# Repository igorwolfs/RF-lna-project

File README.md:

# RF-LNA-Project
This repo contains the kicad-schematics and simulations for 3 separate projects.

[Design, simulation and verification of an 868 MHz, 2-Stage Cascode amplifier](resources/lna/README.md)

[Design, simulation and verification of an 868 MHz Meandered Monopole antenna](https://github.com/igorwolfs/RF-simulations/tree/main/rf_simulations/lorawan_meandered_monopole)

[Design, simulation and verification of an 868 MHz, Single-Gain Stage amplifier](resources/lna/README.md)

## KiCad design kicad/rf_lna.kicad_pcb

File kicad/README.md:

# KiCad Schematics

## Cascode and Single-Gain Stage
### Input voltage
Assume a max input voltage of 1 mV (close to the transceiver) at 868 MHz.
Given a gain of 25 dB.

### Current variation
Current amplitude is somewhere between 18.4 -> 25.6 mA at the oscillation frequency (which is pretty huge).

So required charge over half a period is (25.6-18.4) * (T/2) =  (25.6-18.4)e-3/ (868e6 * 2) = 4.15 pC

Make sure the capacitor arrays carry at least that amount of charge at 5 V.
So 4.15 pC / 5 V < 1 pF, so the capacitor needs to be at least 1 pF (easy).

### Supply voltage
Pick 5 V supply voltage with component L78L05 (cheap, basic component).

Add LED to verify power ON.

### Capacitors
Capacitor Q-factor: capacitor's reactance / capacitor's parasitic resistance.
- The bigger Q, the smaller the ESR relative to the reactance, the better.

### Inductors
Finding a good AC blocking inductor that is
- About 100 nH
- Self resonant-frequency beyond 2 GHz
Seems to be quite the task

### Resistor size
- Always choose smallest package with relevant power rating, to minimize parasitics.
- Probably good up to a few GHz, once going above 2 GHz make sure to get specialized once.

### Thermal relieves
To make soldering the matching components easier, use thermal relieves.

## Antenna

### Design
#### Matching circuit
Estimated using [SimNec](https://www.ae6ty.com/smith_charts/) and [OpenEMS](https://www.openems.de/).

#### CPW to antenna transition
Non-ideal, was a guess based on a quick search for ideal impedance transition methods.

### Simulations
Simulation data for the antenna can be found inside the [rf-simulations repo](https://github.com/igorwolfs/RF-simulations/tree/main/rf_simulations/lorawan_meandered_monopole).

### Verification
Initial verification results using a NanoVNA show similar results to the OpenEMS simulation.

## JLCPCB Stackup
The jlcpcb-[trace impedance calculator](https://jlcpcb.com/pcb-impedance-calculator
) tool was used for trace thickness calculations for our coplanar waveguide. Stackup: JLC04161H-3313 (economic PCBA).

For the following stackup:
- L1: CU: 0.035 mm
- prepreg: 0.2104 mm prepreg
- L2: 0.0152 mm copper
- Core: 1.065 mm
- L3: 0.0152 mm copper
- Prepreg: 7628, RC 49 %, 0.2104 mm
- L4: CU: 0.035 mm

Use a coplanar waveguide.
- distance to surrounding ground: 0.3 mm
- Trace width: 0.3244 mm
    -> So the total CPW is about 0.3244+0.6 = 0.9244 mm.
    -> We do have enough space however so that should not be an issue.

Note: to much distance between GND and trace requires the trace to become wider.

## Checks before ordering
- Component check: 
    - Do all components have the expected value
    - Do all components have the expected footprint size
- Gerber check:
    - Are the groundplanes adequately removed, is there ground plane where there needs to be.
    - Are the components connected as they are supposed to?

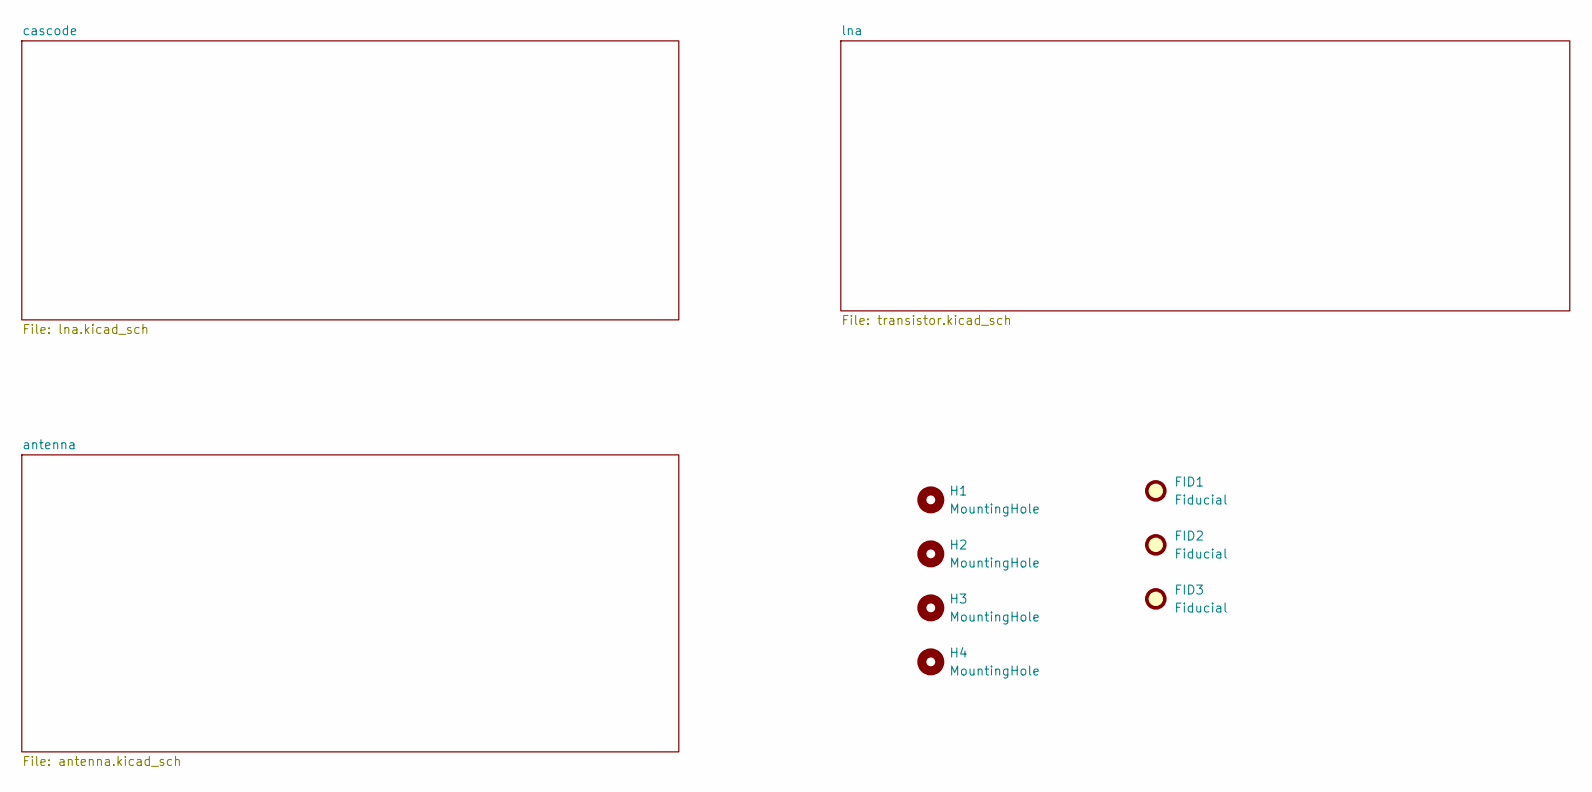
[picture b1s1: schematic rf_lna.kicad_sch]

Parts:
FID1, FID2, FID3: Fiducial; Fiducial_1mm_Mask2mm
H1, H2, H3, H4: MountingHole; MountingHole_1.152mm_jlcpcb

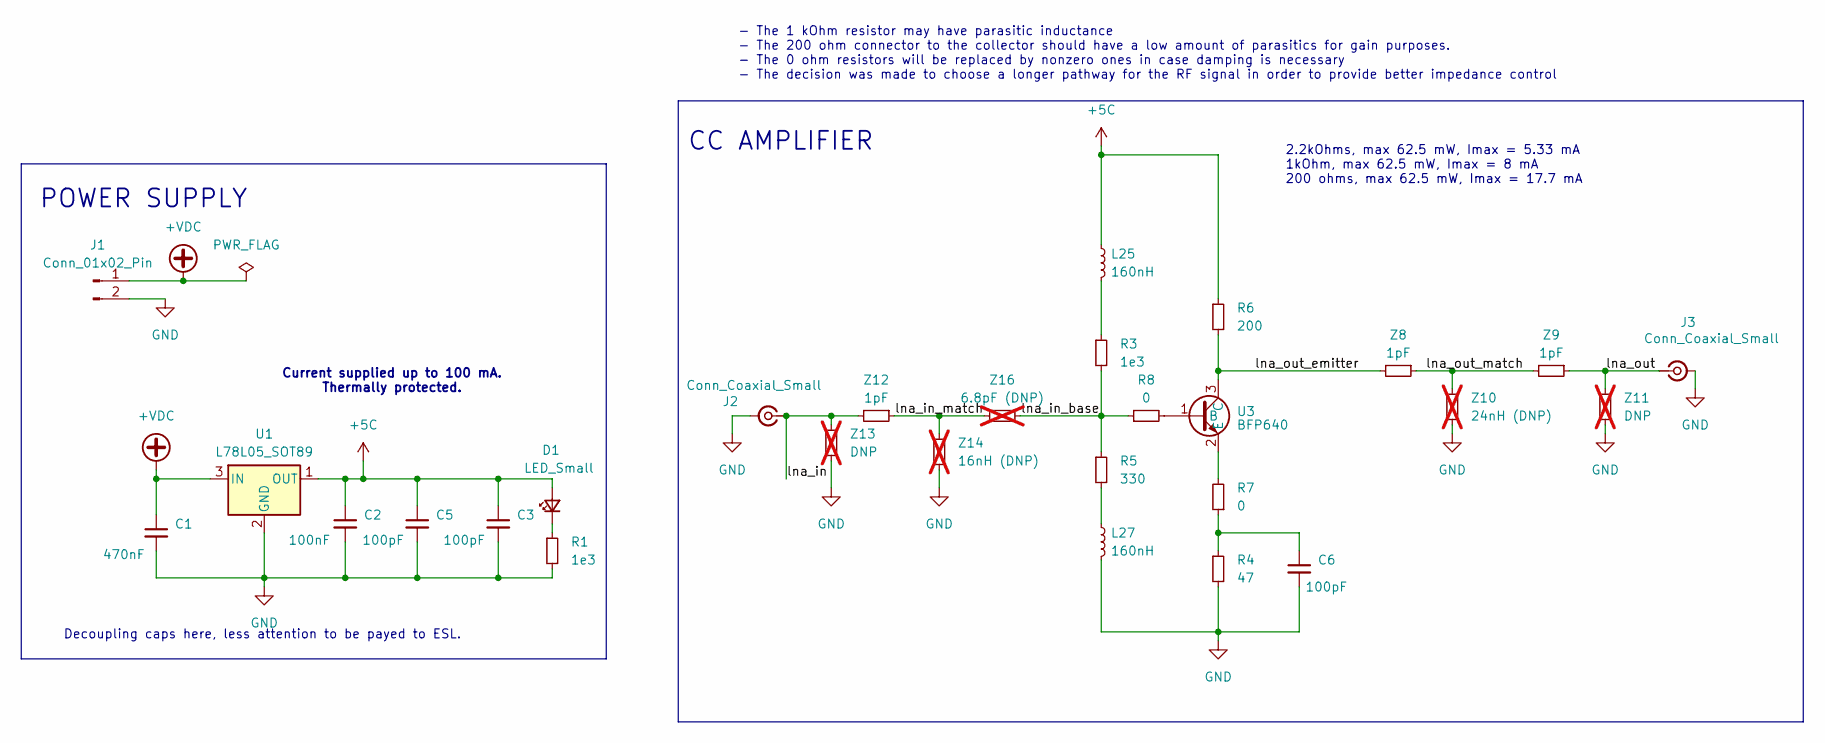
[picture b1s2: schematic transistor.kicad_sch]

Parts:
C1: 470nF; C_0603_1608Metric; Manufacturing Part Numb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 CL10B474KA8NNNC; LCSC Part Number C1623
C2: 100nF; C_0402_1005Metric; Manufacturing Part Numb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 CL05B104KO5NNNC; LCSC Part Number C1525
C3, C5, C6: 100pF; C_0402_1005Metric; Manufacturing Part Numb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 0402CG101J500NT; LCSC Part Number C1546
D1: LED_Small; LED_0603_1608Metric; Manufacturing Part Numb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 KT-0603R; LCSC Part Number C2286
J1: Conn_01x02_Pin; SolderWire-0.25sqmm_1x02_P4.2mm_D0.65mm_OD1.7mm
J2, J3: Conn_Coaxial_Small; SMA_Amphenol_901-143_Vertical; Manufacturing Part Numb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 BWSMA-KE-Z001; LCSC Part Number C496549
L25, L27: 160nH; L_0603_1608Metric; Manufacturing Part Numb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 LQW18ANR16J00D; LCSC Part Number C140445
R1, R3: 1e3; R_0402_1005Metric; Manufacturing Part Numb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 0402WGF1001TCE; LCSC Part Number C11702
R4: 47; R_0603_1608Metric; Manufacturing Part Numb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 0603WAF470JT5E; LCSC Part Number C23182
R5: 330; R_0402_1005Metric; Manufacturing Part Numb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 0402WGF3300TCE; LCSC Part Number C25104
R6: 200; R_0402_1005Metric; Manufacturing Part Numb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 0402WGF2000TCE; LCSC Part Number C25087
R7, R8: 0; R_0402_1005Metric_Pad0.72x0.64mm_HandSolder; Manufacturing Part Numb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 0402WGF0000TCE; LCSC Part Number C17168
U1: L78L05_SOT89; SOT-89-3; Manufacturing Part Numb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 78L05G-AB3-R; LCSC Part Number C71136
U3: BFP640; Manufacturing Part Numb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 BFP640H6327; LCSC Part Number C439781
Z8, Z9, Z12: 1pF; R_0402_1005Metric_Pad0.72x0.64mm_HandSolder; Manufacturing Part Numb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 0402CG1R0C500NT; LCSC Part Number C1550
Z10: 24nH (DNP); R_0402_1005Metric_Pad0.72x0.64mm_HandSolder; not fitted
Z11, Z13: DNP; R_0402_1005Metric_Pad0.72x0.64mm_HandSolder; not fitted
Z14: 16nH (DNP); R_0402_1005Metric_Pad0.72x0.64mm_HandSolder; not fitted
Z16: 6.8pF (DNP); R_0402_1005Metric_Pad0.72x0.64mm_HandSolder; not fitted

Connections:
+5C: C2.1, C3.1, C5.1, D1.2 (A), L25.1, R6.1, U1.1 (OUT)
+VDC: C1.1, J1.1, U1.3 (IN)
/lna/lna_in: J2.1 (In), Z12.2, Z13.2
/lna/lna_in_base: R3.2, R5.1, R8.1, Z16.1
/lna/lna_in_match: Z12.1, Z14.2, Z16.2
/lna/lna_out: J3.1 (In), Z9.1, Z11.2
/lna/lna_out_emitter: R6.2, U3.3 (C), Z8.2
/lna/lna_out_match: Z8.1, Z9.2, Z10.2
GND: C1.2, C2.2, C3.2, C5.2, C6.2, J1.2, J2.2 (Ext), J3.2 (Ext), L27.2, R1.2, R4.2, U1.2 (GND), Z10.1, Z11.1, Z13.1, Z14.1; also elsewhere on the board
unnamed: C6.1, R4.1, R7.1
unnamed: D1.1 (K), R1.1
unnamed: L25.2, R3.1
unnamed: L27.1, R5.2
unnamed: R8.2, U3.1 (B)
unnamed: R7.2, U3.2 (E)

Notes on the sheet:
Current supplied up to 100 mA. Thermally protected.
2.2kOhms, max 62.5 mW, Imax = 5.33 mA 1kOhm, max 62.5 mW, Imax = 8 mA 200 ohms, max 62.5 mW, Imax = 17.7 mA
CC AMPLIFIER
POWER SUPPLY
Decoupling caps here, less attention to be payed to ESL.
- The 1 kOhm resistor may have parasitic inductance - The 200 ohm connector to the collector should have a low amount of parasitics for gain purposes. - The 0 ohm resistors will be replaced by nonzero ones in case damping is necessary - The decision was made to choose a longer pathway for the RF si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

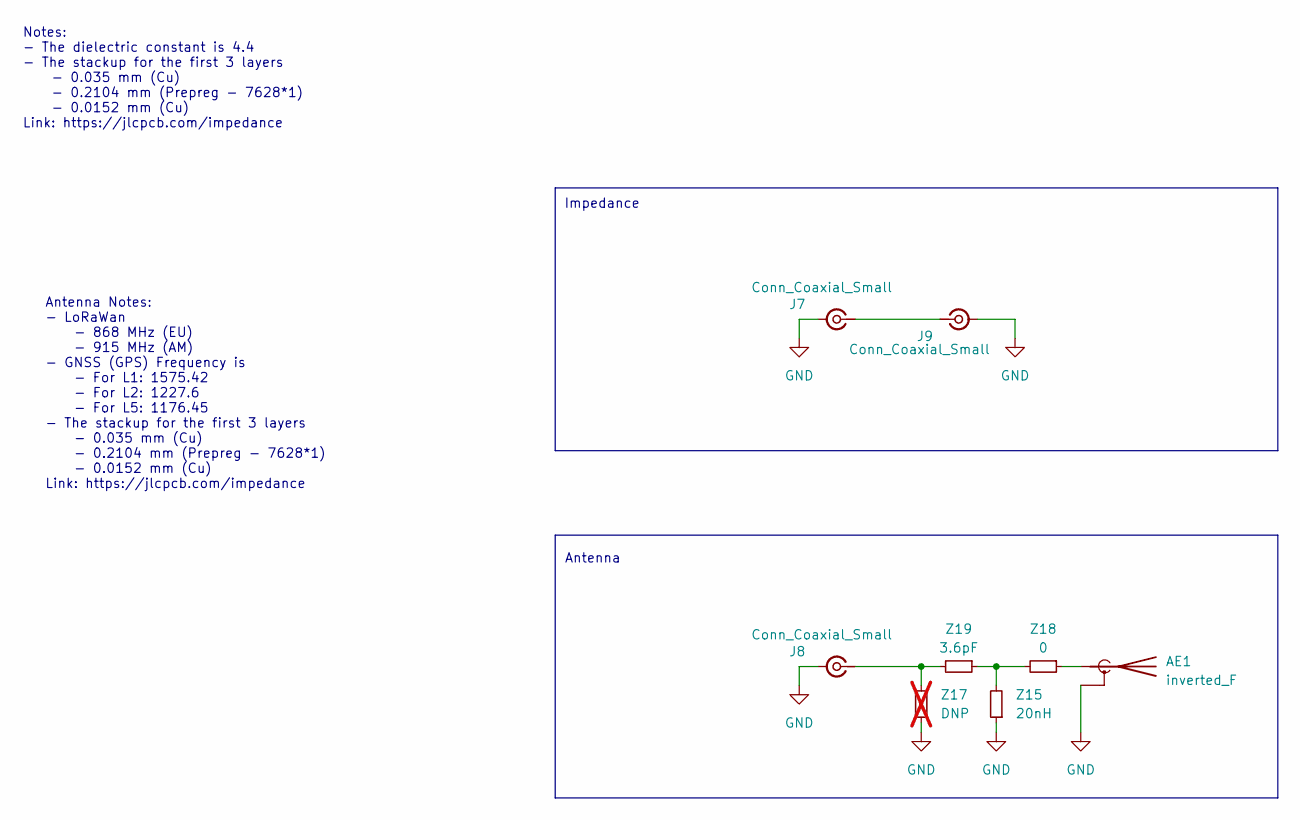
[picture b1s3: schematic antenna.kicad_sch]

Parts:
AE1: inverted_F; iw_meandered_monopole
J7, J8, J9: Conn_Coaxial_Small; SMA_Amphenol_901-143_Vertical; Manufacturing Part Numb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 BWSMA-KE-Z001; LCSC Part Number C496549
Z15: 20nH; R_0402_1005Metric_Pad0.72x0.64mm_HandSolder; Manufacturing Part Numb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 SDCL1005C20NJTDF; LCSC Part Number C96730
Z17: DNP; R_0402_1005Metric_Pad0.72x0.64mm_HandSolder; not fitted
Z18: 0; R_0402_1005Metric_Pad0.72x0.64mm_HandSolder; Manufacturing Part Numb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 0402WGF0000TCE; LCSC Part Number C17168
Z19: 3.6pF; R_0402_1005Metric_Pad0.72x0.64mm_HandSolder; Manufacturing Part Numb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 GJM1555C1H3R6WB01D; LCSC Part Number C161321

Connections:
GND: AE1.2 (GND), J7.2 (Ext), J8.2 (Ext), J9.2 (Ext), Z15.1, Z17.1; also elsewhere on the board
unnamed: AE1.1 (A), Z18.1
unnamed: J7.1 (In), J9.1 (In)
unnamed: J8.1 (In), Z17.2, Z19.2
unnamed: Z15.2, Z18.2, Z19.1

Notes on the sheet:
Antenna
Impedance
Antenna Notes: - LoRaWan - 868 MHz (EU) - 915 MHz (AM) - GNSS (GPS) Frequency is - For L1: 1575.42 - For L2: 1227.6 - For L5: 1176.45 - The stackup for the first 3 layers - 0.035 mm (Cu) - 0.2104 mm (Prepreg - 7628*1) - 0.0152 mm (Cu) Link: https://jlcpcb.com/impedance
Notes: - The dielectric constant is 4.4 - The stackup for the first 3 layers - 0.035 mm (Cu) - 0.2104 mm (Prepreg - 7628*1) - 0.0152 mm (Cu) Link: https://jlcpcb.com/impedance

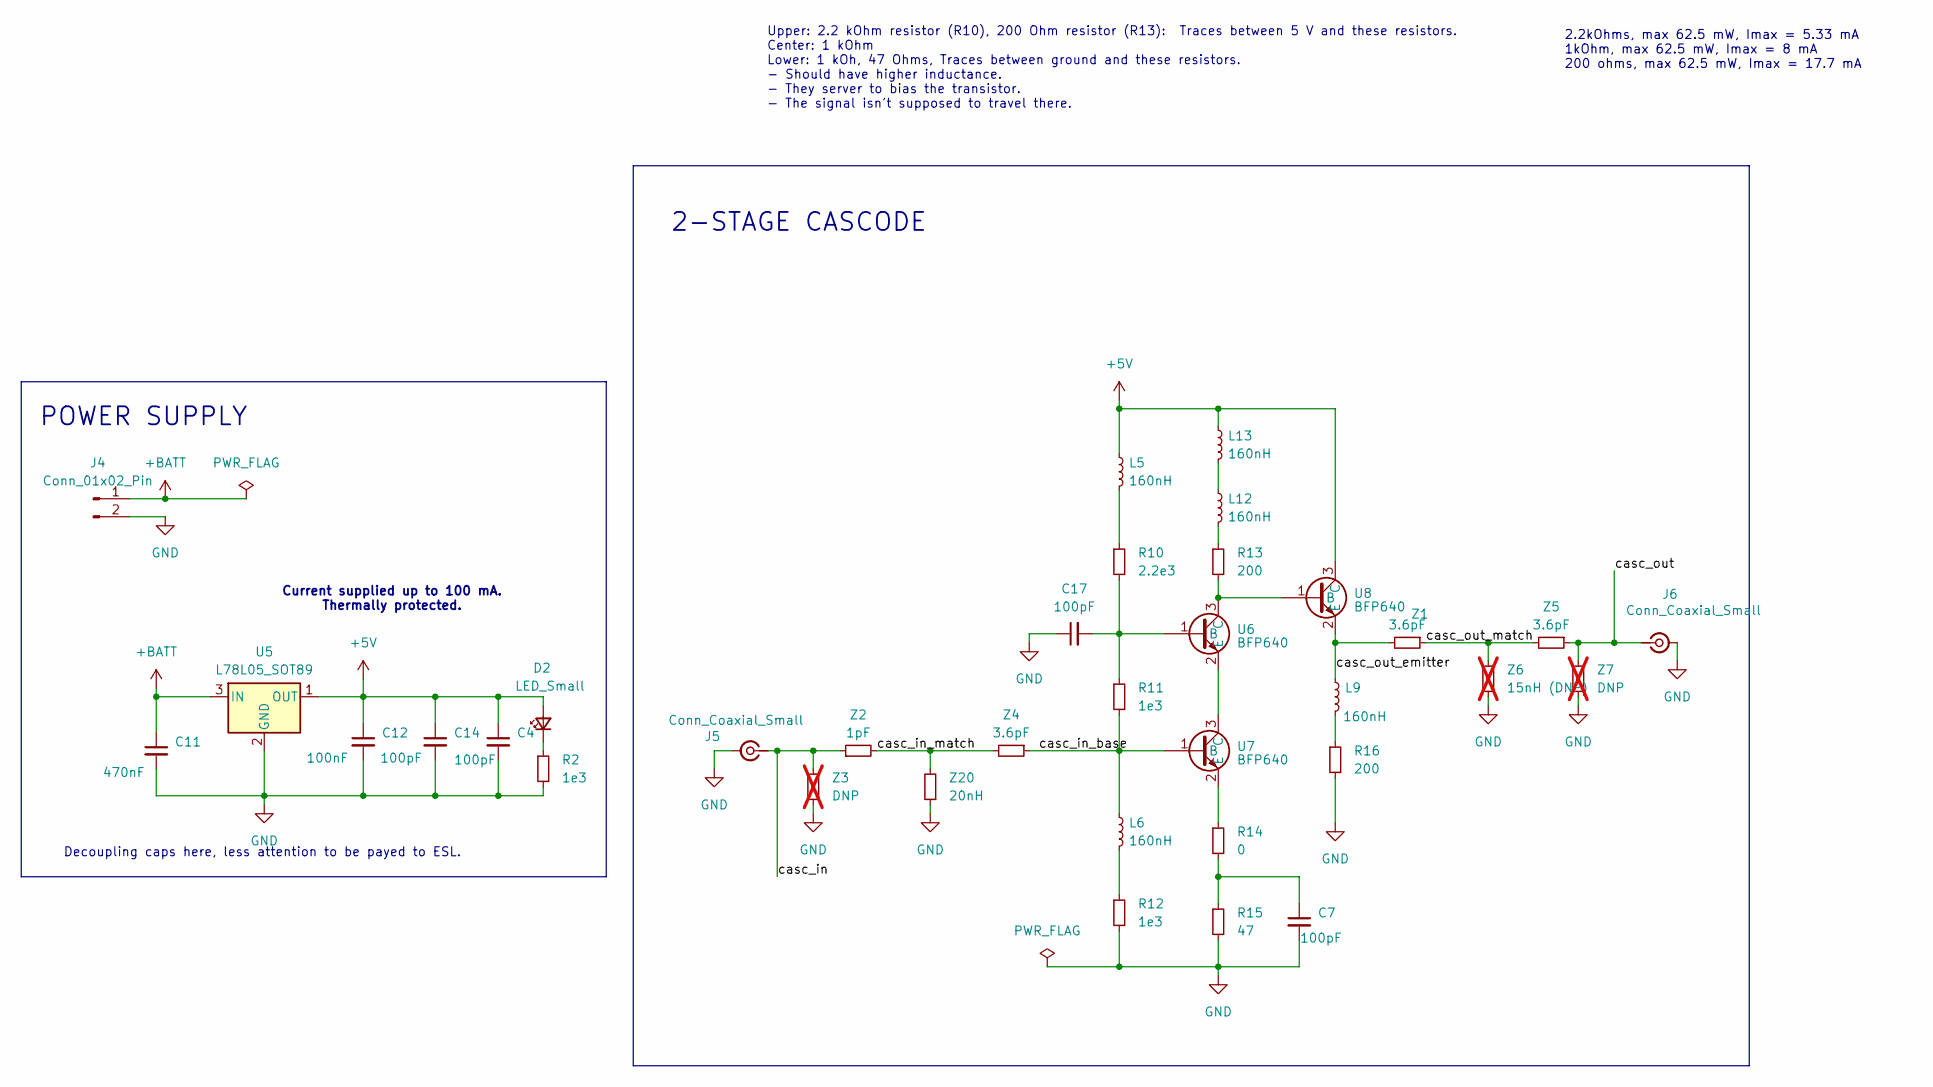
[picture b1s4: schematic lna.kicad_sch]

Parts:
C4, C7, C14, C17: 100pF; C_0402_1005Metric; Manufacturing Part Numb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 0402CG101J500NT; LCSC Part Number C1546
C11: 470nF; C_0603_1608Metric; Manufacturing Part Numb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 CL10B474KA8NNNC; LCSC Part Number C1623
C12: 100nF; C_0402_1005Metric; Manufacturing Part Numb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 CL05B104KO5NNNC; LCSC Part Number C1525
D2: LED_Small; LED_0603_1608Metric; Manufacturing Part Numb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 KT-0603R; LCSC Part Number C2286
J4: Conn_01x02_Pin; SolderWire-0.25sqmm_1x02_P4.2mm_D0.65mm_OD1.7mm
J5, J6: Conn_Coaxial_Small; SMA_Amphenol_901-143_Vertical; Manufacturing Part Numb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 BWSMA-KE-Z001; LCSC Part Number C496549
L5, L6, L9, L12, L13: 160nH; L_0603_1608Metric; Manufacturing Part Numb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 LQW18ANR16J00D; LCSC Part Number C140445
R2, R11, R12: 1e3; R_0402_1005Metric; Manufacturing Part Numb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 0402WGF1001TCE; LCSC Part Number C11702
R10: 2.2e3; R_0402_1005Metric; Manufacturing Part Numb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 0402WGF2201TCE; LCSC Part Number C25879
R13, R16: 200; R_0402_1005Metric; Manufacturing Part Numb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 0402WGF2000TCE; LCSC Part Number C25087
R14: 0; R_0402_1005Metric_Pad0.72x0.64mm_HandSolder; Manufacturing Part Numb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 0402WGF0000TCE; LCSC Part Number C17168
R15: 47; R_0603_1608Metric; Manufacturing Part Numb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 0603WAF470JT5E; LCSC Part Number C23182
U5: L78L05_SOT89; SOT-89-3; Manufacturing Part Numb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 78L05G-AB3-R; LCSC Part Number C71136
U6, U7, U8: BFP640; Manufacturing Part Numb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 BFP640H6327; LCSC Part Number C439781
Z1, Z4, Z5: 3.6pF; R_0402_1005Metric_Pad0.72x0.64mm_HandSolder; Manufacturing Part Numb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 GJM1555C1H3R6WB01D; LCSC Part Number C161321
Z2: 1pF; R_0402_1005Metric_Pad0.72x0.64mm_HandSolder; Manufacturing Part Numb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 0402CG1R0C500NT; LCSC Part Number C1550
Z3, Z7: DNP; R_0402_1005Metric_Pad0.72x0.64mm_HandSolder; not fitted
Z6: 15nH (DNP); R_0402_1005Metric_Pad0.72x0.64mm_HandSolder; not fitted
Z20: 20nH; R_0402_1005Metric_Pad0.72x0.64mm_HandSolder; Manufacturing Part Numb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 SDCL1005C20NJTDF; LCSC Part Number C96730

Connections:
+5V: C4.1, C12.1, C14.1, D2.2 (A), L5.1, L13.1, U5.1 (OUT), U8.3 (C)
+BATT: C11.1, J4.1, U5.3 (IN)
/cascode/casc_in: J5.1 (In), Z2.1, Z3.1
/cascode/casc_in_base: L6.1, R11.2, U7.1 (B), Z4.1
/cascode/casc_in_match: Z2.2, Z4.2, Z20.2
/cascode/casc_out: J6.1 (In), Z5.1, Z7.2
/cascode/casc_out_emitter: L9.1, U8.2 (E), Z1.2
/cascode/casc_out_match: Z1.1, Z5.2, Z6.2
GND: C4.2, C7.2, C11.2, C12.2, C14.2, C17.1, J4.2, J5.2 (Ext), J6.2 (Ext), R2.2, R12.2, R15.2, R16.2, U5.2 (GND), Z3.2, Z6.1, Z7.1, Z20.1; also elsewhere on the board
unnamed: C7.1, R14.2, R15.1
unnamed: D2.1 (K), R2.1
unnamed: L5.2, R10.1
unnamed: L6.2, R12.1
unnamed: L9.2, R16.1
unnamed: L12.1, L13.2
unnamed: L12.2, R13.1
unnamed: C17.2, R10.2, R11.1, U6.1 (B)
unnamed: R13.2, U6.3 (C), U8.1 (B)
unnamed: U6.2 (E), U7.3 (C)
unnamed: R14.1, U7.2 (E)

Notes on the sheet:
2-STAGE CASCODE
2.2kOhms, max 62.5 mW, Imax = 5.33 mA 1kOhm, max 62.5 mW, Imax = 8 mA 200 ohms, max 62.5 mW, Imax = 17.7 mA
Upper: 2.2 kOhm resistor (R10), 200 Ohm resistor (R13): Traces between 5 V and these resistors. Center: 1 kOhm Lower: 1 kOh, 47 Ohms, Traces between ground and these resistors. - Should have higher inductance. - They server to bias the transistor. - The signal isn't supposed to travel there.
Current supplied up to 100 mA. Thermally protected.
Decoupling caps here, less attention to be payed to ESL.
POWER SUPPLY

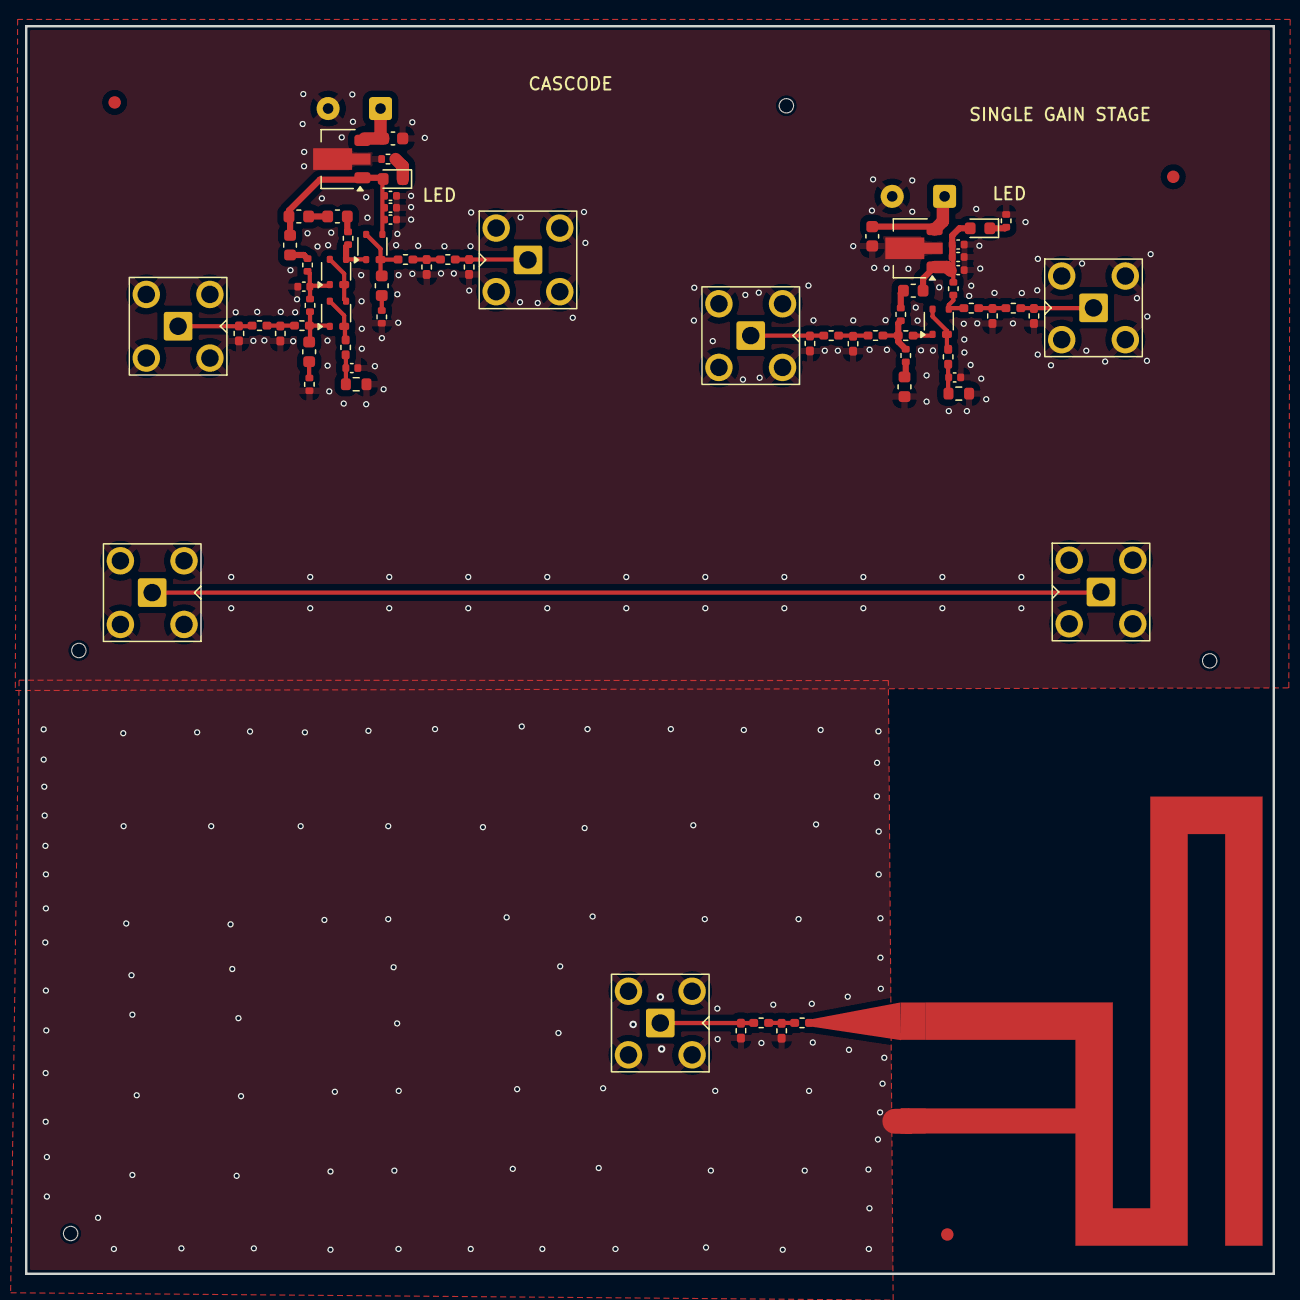
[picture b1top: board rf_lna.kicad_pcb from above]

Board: 4 copper layers, 100.0 x 100.0 mm, 78 parts (0 on the bottom side), 38 nets.

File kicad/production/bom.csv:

Designator,Footprint,Quantity,Value,LCSC Part #
AE1,iw_meandered_monopole,1,inverted_F,
"C1, C11",603,2,470nF,
"C12, C2",402,2,100nF,
"C14, C17, C3, C4, C5, C6, C7",402,7,100pF,
"D1, D2",603,2,LED_Small,
"J1, J4",SolderWire-0.25sqmm_1x02_P4.2mm_D0.65mm_OD1.7mm,2,Conn_01x02_Pin,
"J2, J3, J5, J6, J7, J8, J9",SMA_Amphenol_901-143_Vertical,7,Conn_Coaxial_Small,
"L12, L13, L25, L27, L5, L6, L9",603,7,160nH,
"R1, R11, R12, R2, R3",402,5,1.00E+03,
R10,402,1,2.20E+03,
"R13, R16, R6",402,3,200,
"R14, R7, R8, Z18",402,4,0,
"R15, R4",603,2,47,
R5,402,1,330,
"U1, U5",SOT-89-3,2,L78L05_SOT89,
"U3, U6, U7, U8",BFP640,4,BFP640,
"Z1, Z19, Z4, Z5",402,4,3.6pF,
"Z12, Z2, Z8, Z9",402,4,1pF,
"Z15, Z20",402,2,20nH,

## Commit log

2024-09-24 added notes, added datasheets, | TODO: check how stability analyisis is done, choose BJT, make prototype circuit
2024-09-24 added gitignore
2024-09-24 removed application notes for space reasons
2024-09-25 added notes
2024-09-28 [simulatinos] Did some basic experiments [resources] Tried calculating resistor values, currents and voltages, erroneous results however
2024-10-01 updated gitignore
2024-10-01 [resources] Added (correct) LNA calculations assuming infinite load, added stability calculations [simulations] Added single stage LNA simulations for 3.3 and 5 V Vcc
2024-10-01 [resources] Added emitter-follower dimensioning | TODO: answer questions in notebook + simulate emitter-follower circuit
2024-10-02 [simulations] Added emitter follower simulations, added frequency sweep simulation | TODO: figure out how to get absolute dB values referenced to the gain in ltspice, check the gain-input-amplitude c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
2024-10-03 [simulations] Fixed gain problem for low amplitudes | TODO: complete small-signal circuit for 2-stage LNA
2024-10-06 [simulations] Added cacscode amplifier, did input impedance matching, checked stability, checked s-parameters, did noise simulations | TODO: check actual noise factor simulations
2024-10-06 Fix the bias-T's in the noise-test simulation or look for example simulations for such test circuits
2024-10-08 [simulations] Noise factor simulation complete | TODO: introduce matching circuits, match impedances and recalculate reflection, transmission, noise, etc..
2024-10-08 finished impedance matching and S-parameter analysis
2024-12-07 [simulations] Simply added rf-netlist [lna_schematics] Started with kicad schematic
2024-12-07 minor changes
2024-12-18 [simulations] Added L-matching networks | TODO: find wide-band matching T / Pi matching circuits (800MHz -> 1.5 GHz), find actual working components for the circuit
2024-12-18 test
2024-12-19 [lna_schematics] Simulated with matched impedance to get voltage values and verify matching parameters [lna_schematics] Added matched elements, added notes
2024-12-20 [kicad] Added various footprints, added matched network
2024-12-20 [simualations] Added simulations for components matching
2024-12-20 [general] Added notes
2024-12-20 [lna_schematics] added final components for impedance matching [simulations] Added final impedance matched simulations | TODO: stackup + layout + footprint check
2024-12-20 [kicad] Finished pads, stackup, symbols for LNA. Starting layout.
2024-12-20 [kicad] Implemement custom design rule for CPW
2024-12-20 [simulations] Switched bypass capacitor to new value
2024-12-21 [simulations] Added extra simulations with inductors | TODO: match impedance with inductors
2024-12-21 [lna_schematics] Added single-transistor LNA to schematics | TODO: update footprint and matched impedance with inductors
2024-12-21 [simulations] Did simulations with matching circuits | TODO: figure out a way to lower the S22 while including a capacitor filter. Check why exactly adding inductors causes the S22 here to be so high
2024-12-23 [lna_schematics] Added components for matching + inductances | TODO: place inductors to prevent capacitive coupling [simulations] Added stability factor and matching circuits | TODO: do bilateral mat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
2024-12-24 [simulations] Did full impedance matching, changed inductors to 160 nH instead of 91
2024-12-24 [rf_lna] did layout of rf amplifiers for LNA | TODO: create an antenna design for the bottom half
2024-12-25 [kicad] Did placement of lna components, added antenna | TODO: connect traces, add extra trace for impedance check, add antenna
2024-12-28 [kicad] Added antenna footprint to PCB | TODO: simulate and then add the antenna to the gerber as a whole
2025-01-09 impedance checks + minor changes
2025-01-12 changed gitignore
2025-01-12 [simulations] Moved simulations for antenna into folder
2025-01-12 [simulations] Reorganized ltspice simulations, checked use of transmission line simulation, checked stability and asked stability question
2025-01-12 removed simulation data
2025-01-12 [review] Added questions for review
2025-01-12 reorganized kicad schematics
2025-01-12 [kicad] Added routing, antenna footprint creation, via stitching, fencing, added extra matching footprints, removed footprints from BOM -> perform matching on receipt of PCB itself, added 78 mm - 50 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
2025-01-12 [kicad] Removed excess dimensioning on antenna, added extra vias around sma connector
2025-01-13 added pictures of boards and reddit message. Added 3D models in kicad
2025-01-18 files ready for production, but with wrong stackup (3313)
2025-01-18 placed jlcpcb order, waiting for gerber confirmation
2025-03-22 [minor] Added LNA readme
2025-03-24 [feat] Cleaned up README's
2025-04-01 [bringup] Added calibration data for 2-port and single-port system with coax, added markdown
2025-04-02 [bringup] Added antenna measurement results and todos
2025-04-03 [minor] Added todo's for next version
2025-04-03 [bringup] Added 2-port VNA measurements version 1 and 2, added comments for first antenna matching step, changed antenna calibration data [next] Check reason for single-gain stage failure
2025-04-03 [bringup] Added notes on transistor operating mode [next] Calculate matching circuits, add soldering bridge to lna
2025-04-04 [bringup] Got RF matching circuit, added todo's and next steps for future circuits, [next] Merging 2-way s-parameter circuits
2025-04-05 [bringup - antenna] Optimal matching verification and rematch using scikit-rf lib
2025-04-05 [bringup] Added stability check + gain check for LNA [next] Create a model of the LNA using the S-parameters from the website, check the model results vs real results, see where best to apply damping
2025-04-05 [bringup] Checked stability conditions (mu, rollet, circles), added s-parameter data for simulation purposes [next] Interpolate and simulate the single-gain stage, do the same with the LNA, check LNA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
2025-04-05 [minor] Changed readme
2025-04-06 [bringup] Added interpolation of transistor parameters, added 3rd port, building circuits for the single-gain stage
2025-04-06 [bringup] Cleaned up code, put everything into single python-libs repo, added s-port transform resource, added transforms from common-emitter to common-base and common-collector
2025-04-07 [bringup] Finished circuit drawing, change frequency range and check s-parameters
2025-04-07 [bringup] Finished circuit construction [next] Actually calculated the correct common-base and common-collector s-parameter matrices, then extend them with a ground-prot
2025-04-08 [bringup] Finished simulations, [next] Solder shorts in matching circuit and measure for matching
2025-05-11 [kicad] Update to kicad 9
2025-05-11 [antenna] Added 2 measurements + conclusions
2025-05-11 [cascode] Wrote down conclusions (next) match using SimNec / manually, physically finish matching
2025-05-11 [cascode] Added comments on matching (next) make sure to do manual matching / separate matching
2025-12-07 minor change
